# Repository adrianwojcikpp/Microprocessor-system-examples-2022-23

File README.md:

# Microprocessor systems exampels
Microprocessor systems (I) laboratory classes exampels

Examples of digital circuits and CLI applications based on Microprocessor systems laboratory classes on Automatic Control and Robotics at the Poznań University of Technology.

For editing '.circ' files use Logisim 2.7.0: http://www.cburch.com/logisim/index.html or Logisim Evolution: https://github.com/logisim-evolution/logisim-evolution

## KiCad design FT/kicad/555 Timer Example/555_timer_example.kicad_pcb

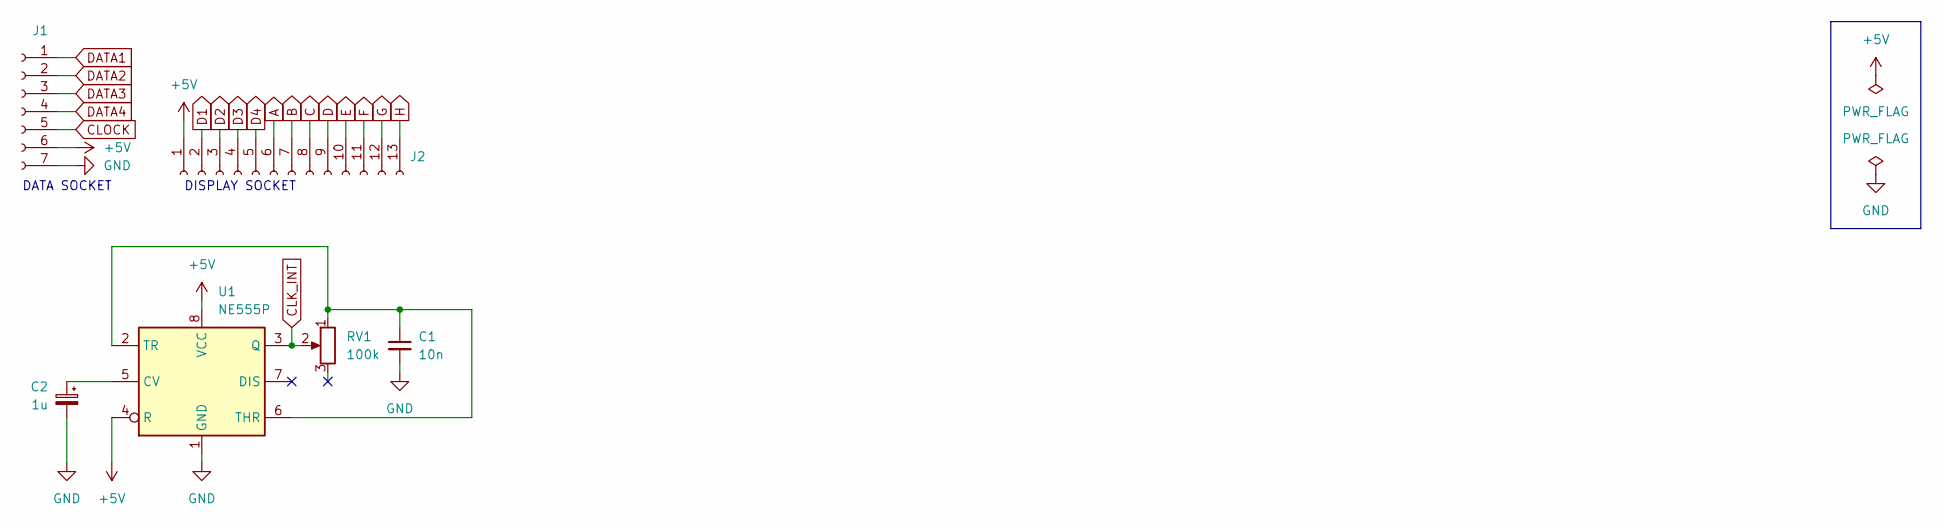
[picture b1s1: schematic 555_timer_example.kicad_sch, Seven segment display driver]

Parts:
C1: 10n; C_Disc_D4.7mm_W2.5mm_P5.00mm
C2: 1u; CP_Radial_D5.0mm_P2.50mm
J1: Conn_01x07_Socket; PinSocket_1x07_P2.54mm_Horizontal
J2: Conn_01x13_Socket; PinSocket_1x13_P2.54mm_Vertical
RV1: 100k; Potentiometer_Bourns_3386F_Vertical
U1: NE555P; DIP-8_W7.62mm

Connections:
+5V: J1.6, J2.1, U1.4 (R), U1.8 (VCC)
A: J2.6
B: J2.7
C: J2.8
CLK_INT: RV1.2, U1.3 (Q)
CLOCK: J1.5
D: J2.9
D1: J2.2
D2: J2.3
D3: J2.4
D4: J2.5
DATA1: J1.1
DATA2: J1.2
DATA3: J1.3
DATA4: J1.4
E: J2.10
F: J2.11
G: J2.12
GND: C1.2, C2.2, J1.7, U1.1 (GND)
H: J2.13
unnamed: C2.1, U1.5 (CV)
unnamed: C1.1, RV1.1, U1.2 (TR), U1.6 (THR)

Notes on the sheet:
DISPLAY SOCKET
DATA SOCKET

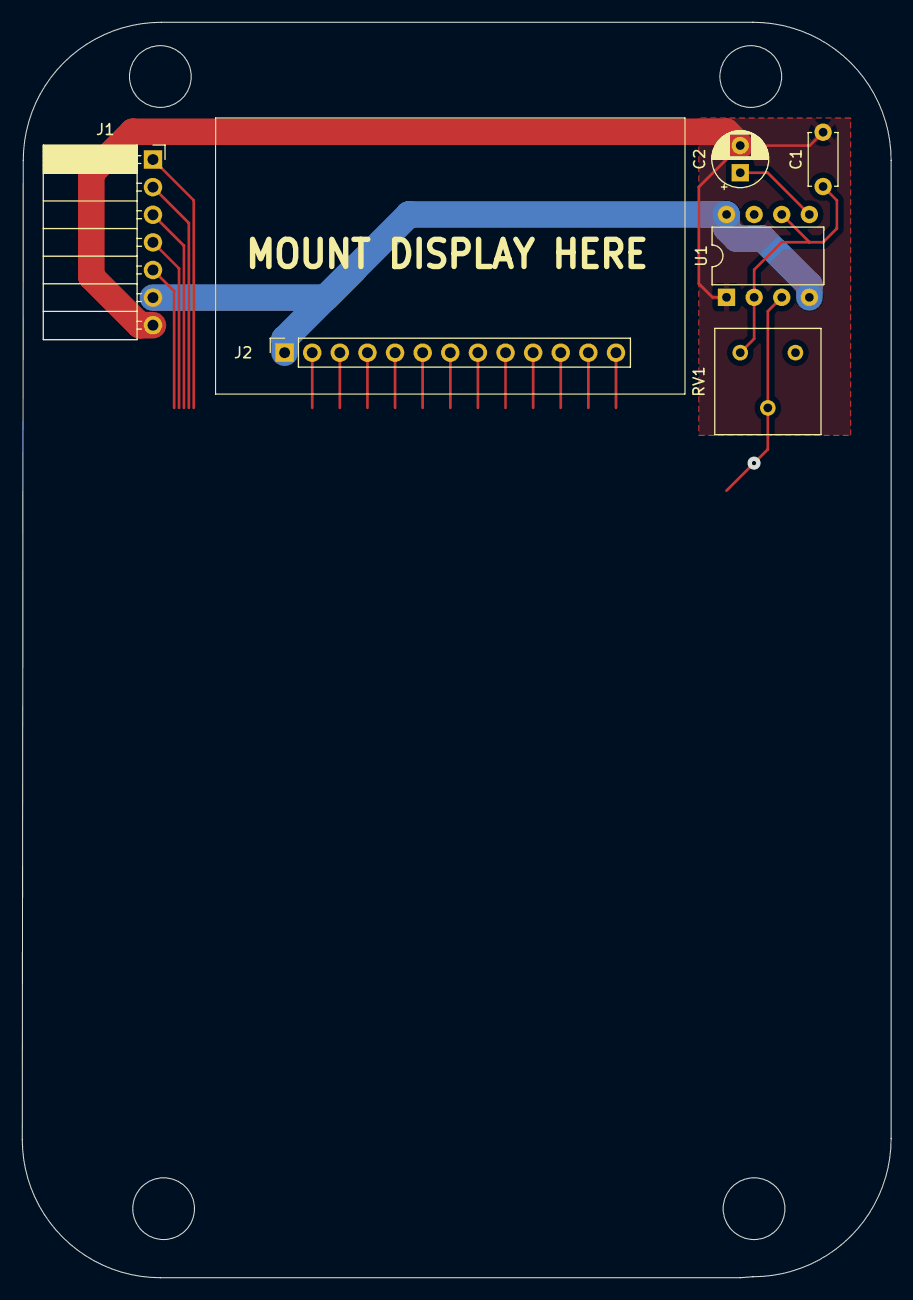
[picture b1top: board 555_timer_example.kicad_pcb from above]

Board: 2 copper layers, 79.9 x 115.5 mm, 6 parts (0 on the bottom side), 5 nets.

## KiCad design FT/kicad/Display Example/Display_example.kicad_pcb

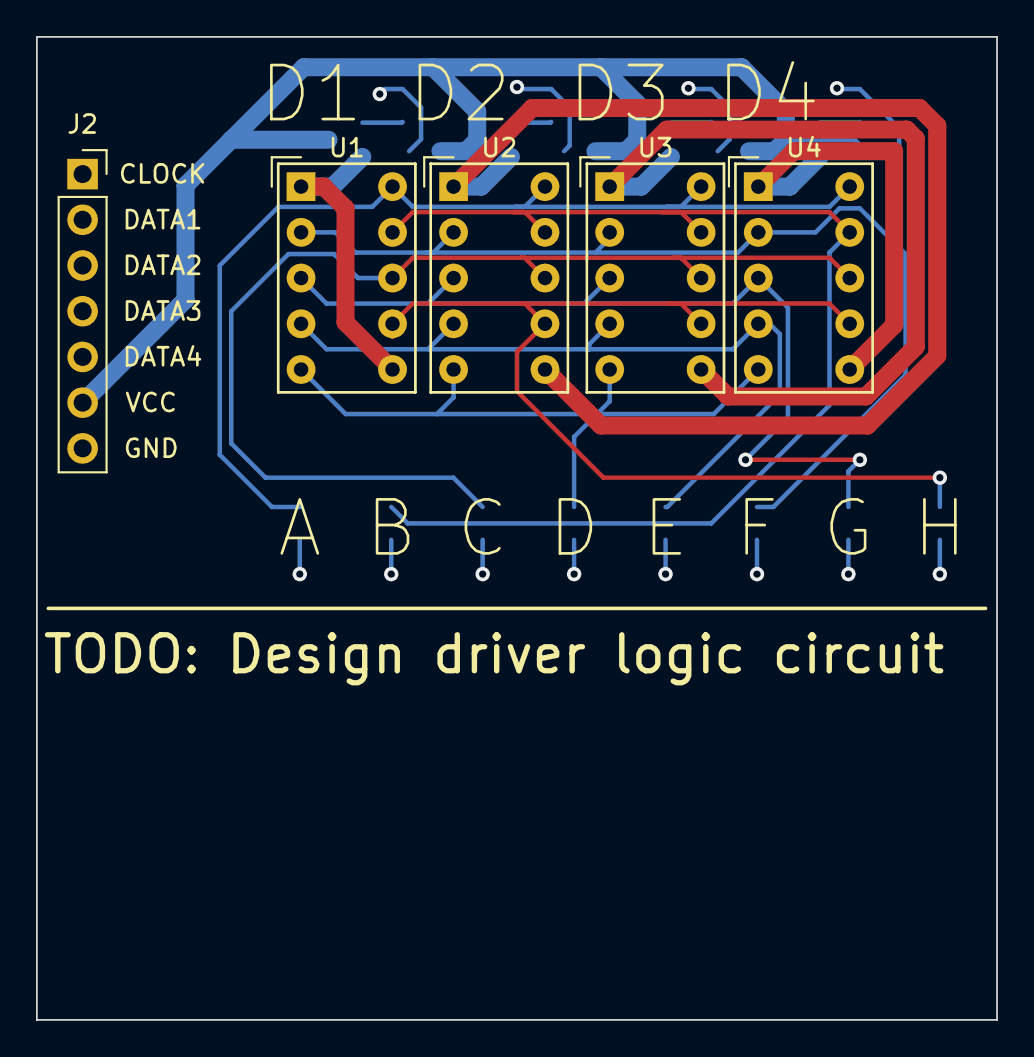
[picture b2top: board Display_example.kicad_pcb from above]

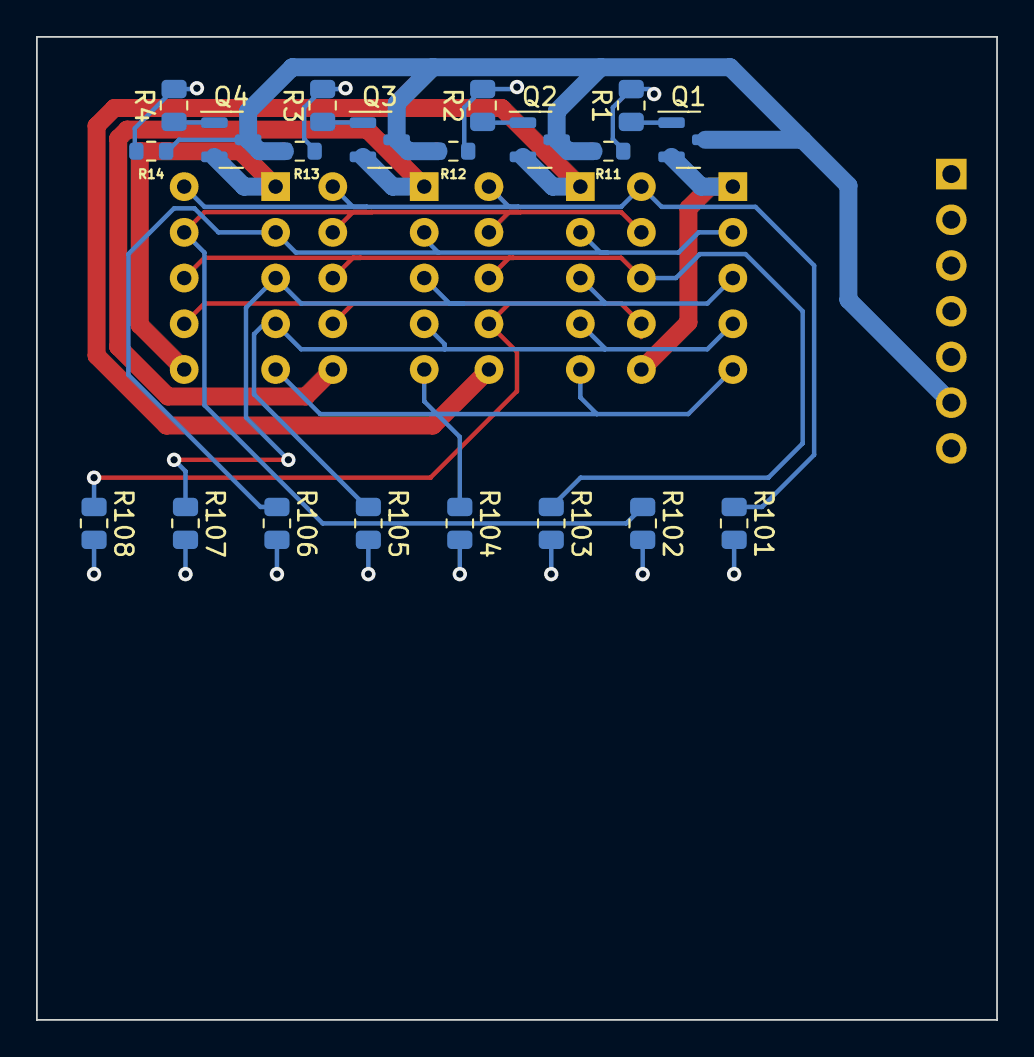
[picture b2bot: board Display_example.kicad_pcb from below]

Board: 2 copper layers, 53.3 x 54.6 mm, 25 parts (20 on the bottom side), 21 nets.

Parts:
J2: Conn_01x07_Socket; PinSocket_1x07_P2.54mm_Vertical
Q1, Q2, Q3, Q4: Q_PNP_BCE; SOT-23
R1, R2, R3, R4: 1k; R_0805_2012Metric
R11, R12, R13, R14: 10k; R_0603_1608Metric
R101, R102, R103, R104, R105, R106, R107, R108: 500; R_0805_2012Metric
U1, U2, U3, U4: HDSP-7501; HDSP-A151

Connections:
/Display/D1: R1.2, R11.1
/Display/D2: R2.2, R12.1
/Display/D3: R3.2, R13.1
/Display/D4: R4.2, R14.1
Acom: R101.1, U1.10 (A), U2.10 (A), U3.10 (A), U4.10 (A)
Bcom: R102.1, U1.9 (B), U2.9 (B), U3.9 (B), U4.9 (B)
Ccom: R103.1, U1.8 (C), U2.8 (C), U3.8 (C), U4.8 (C)
Dcom: R104.1, U1.5 (D), U2.5 (D), U3.5 (D), U4.5 (D)
Ecom: R105.1, U1.4 (E), U2.4 (E), U3.4 (E), U4.4 (E)
Fcom: R106.1, U1.2 (F), U2.2 (F), U3.2 (F), U4.2 (F)
Gcom: R107.1, U1.3 (G), U2.3 (G), U3.3 (G), U4.3 (G)
Hcom: R108.1, U1.7 (DP), U2.7 (DP), U3.7 (DP), U4.7 (DP)
unnamed: Q1.1 (B), R1.1
unnamed: Q1.2 (C), U1.1 (CA), U1.6 (CA)
unnamed: Q2.1 (B), R2.1
unnamed: Q2.2 (C), U2.1 (CA), U2.6 (CA)
unnamed: Q3.1 (B), R3.1
unnamed: Q3.2 (C), U3.1 (CA), U3.6 (CA)
unnamed: Q4.1 (B), R4.1
unnamed: Q4.2 (C), U4.1 (CA), U4.6 (CA)
VCC: J2.6, Q1.3 (E), Q2.3 (E), Q3.3 (E), Q4.3 (E), R11.2, R12.2, R13.2, R14.2

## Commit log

2023-02-27 L01 Example
2023-03-06 L02 Examples
2023-03-13 L03 Example
2023-03-21 L04 Example
2023-03-27 Test cases update:
2023-03-27 L05 Examples
2023-04-03 L06 Example
2023-04-17 L07 Examples
2023-04-17 Moore machine v2
2023-04-17 extras examples
2023-04-21 fix input vis
2023-04-24 + 'static const' for look up tables
2023-04-24 L08 Example
2023-04-24 + command line user interface
2023-05-08 L08 Example [hotfix]
2023-05-08 L08 Example [proper fix]
2023-05-08 L09 Example
2023-05-09 L08 Example [macro-based generic printing]
2023-05-09 L09 Examaple
2023-05-15 L09 Example [struct example refactor]
2023-05-26 L10 Example (Win32 API timeout)
2023-05-28 L11 Examples
2023-05-28 Final Task Examples
2023-05-29 L10 Fix
2023-05-29 Final Task example
2023-06-05 Final Task Example
    npn to pnp
2024-02-26 L01 LTspice input waveform change
2024-02-26 misspelled comment
2024-03-18 pos_to_nor powershell script update
    + NOR gate translation do the right
    + Changing NOTs sizes to 'narrow'
    + Adding missing wires
2024-04-16 L07 Example
2024-05-05 L08 Example circuits
2024-05-05 overflow vs saturation undefined behavior
2024-05-06 quick refactor
2024-05-08 L11 STM32 example update
2024-05-30 Final Task part 2
2024-05-31 KiCad update
2024-05-31 SPICE update
2025-04-03 L04 Example 02 update
    + const modifier for 1. argument of 'read_bit' function
